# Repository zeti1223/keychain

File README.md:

# Keychain NFC Project

This is a KiCad-based NFC keychain project using the NXP NT2H1311F0DTLH NFC Forum Type 2 Tag compliant IC.

## Overview

The project features a compact, printed circuit board (PCB) based NFC keychain with 144 bytes of user memory and field detection capabilities.

### 3D Renders

### PCB Design

## Features

- **NFC Chip**: NXP NT2H1311F0DTLH
- **NFC Type**: NFC Forum Type 2 Tag compliant
- **Memory**: 144 bytes user memory
- **Antenna**: Integrated loop antenna
- **PCB**: Black, 1.6mm thickness, HASL (with lead) surface finish
- **Size**: Compact keychain-sized design

## Components

### Main components

- **IC1**: NT2H1311F0DTLH - NFC Tag IC (NXP)
- **C1**: Capacitor (Optional)
- **AE1**: NFC antenna (loop antenna)
- **H1**: Keychain hole (5mm)

## Files

- `keychain.kicad_pro` - KiCad project file
- `keychain.kicad_sch` - Schematic
- `keychain.kicad_pcb` - PCB layout
- `images/` - 3D renders and design images
- `production/` - Manufacturing files (BOM, positions, etc.)

## Price List

### Manufacturing costs (JLCPCB)

| Item | Description | Quantity | Lead time | Price |
|------|-------------|----------|-----------|-------|
| PCB prototype | Y7-13303142A, Black, 1.6mm thickness, HASL (with lead) | 5 pcs | 3 days | $4.00 |

### Summary

- **Merchandise Total**: $4.10
- **Shipping Estimated**: $21.44
- **Coupons**: -$10.00
- **Subtotal**: 15.54$
- **Weight**: 0.14kg
- **Est. shipping date**: 2026-08-31

## Manufacturing

The project is optimized for JLCPCB. Manufacturing files are located in the `production/` folder:

- `keychain.zip` - Complete manufacturing package
- `bom.csv` - Bill of materials
- `positions.csv` - Component positions
- `designators.csv` - Component designators
- `netlist.ipc` - Netlist

## NFC Functionality

The NT2H1311F0DTLH chip supports:

- NFC Forum Type 2 Tag standard
- 144 bytes user memory
- Field detection
- Passive operation (no battery required)

## License

See the [LICENSE](LICENSE) file for license details.

## Author

- Created by: Zeti_1223

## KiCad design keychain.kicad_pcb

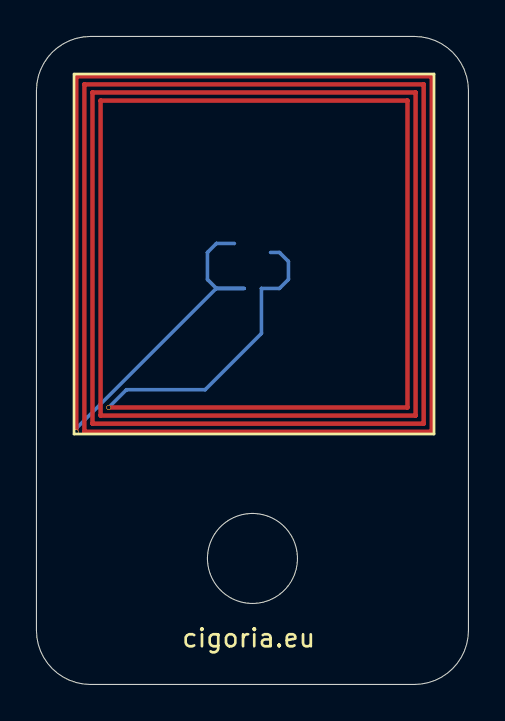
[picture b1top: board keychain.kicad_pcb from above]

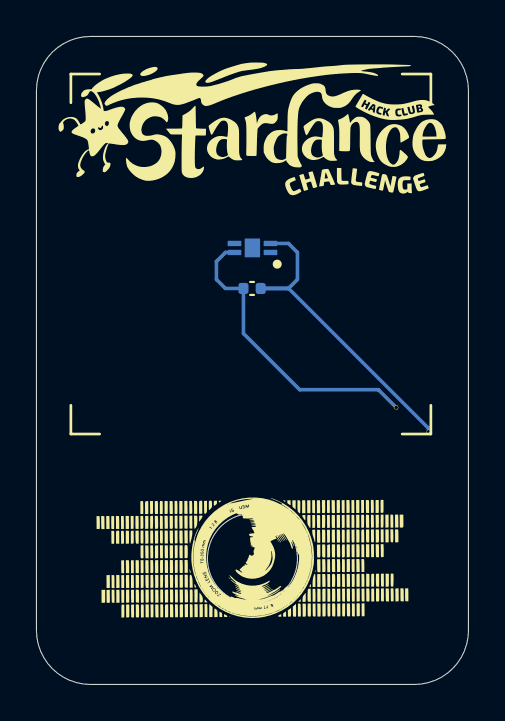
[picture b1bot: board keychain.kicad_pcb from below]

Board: 2 copper layers, 24.0 x 36.0 mm, 4 parts (2 on the bottom side), 2 nets.

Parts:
AE1: Antenna_Loop; nfc_antenna
C1: C_0402_1005Metric
H1: MountingHole; MountingHole_5mm
IC1: NT2H1311F0DTLH; SON50P200X150X50-5N

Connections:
unnamed: AE1.2, C1.2, IC1.4 (LA)
unnamed: AE1.1, C1.1, IC1.2 (LB)
